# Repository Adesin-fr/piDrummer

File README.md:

# piDrummer

piDrummer is a DIY drum trigger device. it uses an Arduino and some basic components to get the signal from your pads (AKA triggers) and send them to a Raspberry Pi 3.

A Raspberry Pi 3 is used to play sounds according to the triggers you hit. 

Thanks to CPU power of a such board computer (4x1.2 Ghz), it is possible to play the best sound quality !

The rPi is also driving an ILI9341 TFT screen (320x240 pixels, can be found as cheap as 5$ on ebay ) and displays an interface that allows you to set up your different drum kits, the volume, sound effects (reverb, equalizer, etc...), and map each trigger to an instrument.

The goal is also to build an embedded linux, with the smallest possible kernel, allowing for very small boot time !

# piDrummer (Version Française)

piDrummer est un module de batterie électronique à fabriquer soi-même.

Il utilise un module Arduino et quelques composants pour récupérer le signal depuis les PADS (aussi appelés Triggers), et envoie ces informations à une carte Raspberry Pi 3.

La carte est alors utilisée pour jouer les sons en fonction des coups donnés.

Grâce à la puissance de calcul disponible sur la carte (4x1.2 Ghz), un rendu sonore de haute qualité est possible !

La carte rPi est aussi utilisée pour piloter un afficheur TFT (320x240 à base de puce ILI9341, qu'on peut acheter sur Ebay pour moins de 5€) afin de régler et choisir vos différents kits, le volume, les effets sonores (reverb, équaliseur, etc...) et mapper chaque trigger à un instrument.

Le but du projet est aussi de monter un système linux embarqué (linux Embedded) avec un noyau le plus léger possible, et un temps de démarrage le plus faible possible !

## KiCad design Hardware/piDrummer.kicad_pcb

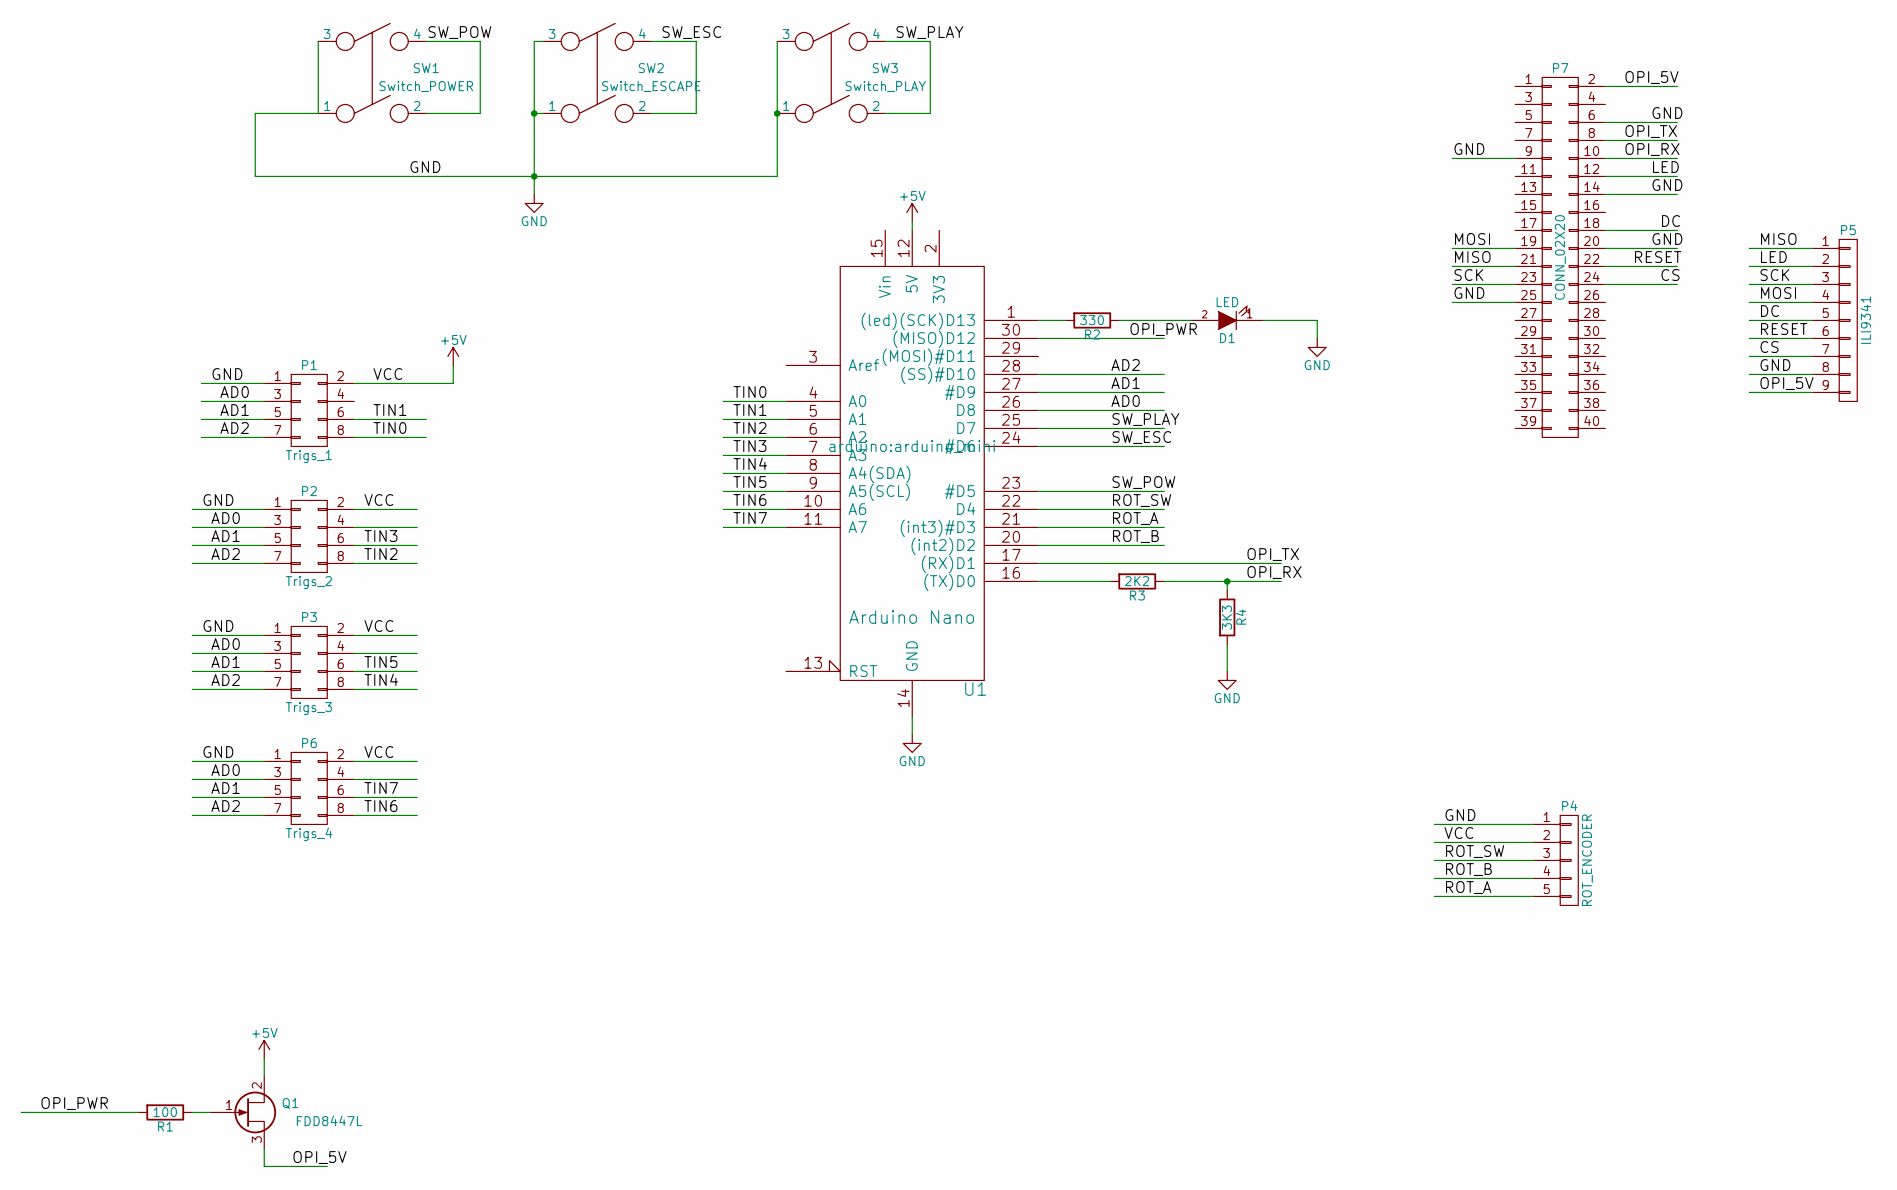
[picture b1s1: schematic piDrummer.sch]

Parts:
D1: LED; LED-3MM
P1: Trigs_1; Pin_Header_Straight_2x04
P2: Trigs_2; Pin_Header_Straight_2x04
P3: Trigs_3; Pin_Header_Straight_2x04
P4: ROT_ENCODER; Pin_Header_Straight_1x05
P5: ILI9341; Pin_Header_Straight_1x09
P6: Trigs_4; Pin_Header_Straight_2x04
P7: CONN_02X20; Pin_Header_Straight_2x20
Q1: FDD8447L; MOSFET_TO252
R1: 100; R4-LARGE_PADS
R2: 330; R4-LARGE_PADS
R3: 2K2; R4-LARGE_PADS
R4: 3K3; R4-LARGE_PADS
SW1: Switch_POWER; NetTie-III
SW2: Switch_ESCAPE; NetTie-III
SW3: Switch_PLAY; NetTie-III
U1: Arduino Nano; arduino_mini

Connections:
+5V: P1.2, P2.2, P3.2, P4.2, P6.2, Q1.2 (D), U1.12 (5V)
/AD0: P1.3, P2.3, P3.3, P6.3, U1.26 (D8)
/AD1: P1.5, P2.5, P3.5, P6.5, U1.27 (#D9)
/AD2: P1.7, P2.7, P3.7, P6.7, U1.28 ((SS)#D10)
/CS: P5.7, P7.24
/DC: P5.5, P7.18
/LED: P5.2, P7.12
/MISO: P5.1, P7.21
/MOSI: P5.4, P7.19
/OPI_5V: P5.9, P7.2, Q1.3 (S)
/OPI_PWR: R1.2, U1.30 ((MISO)D12)
/OPI_RX: P7.10, R3.1, R4.1
/OPI_TX: P7.8, U1.17 ((RX)D1)
/RESET: P5.6, P7.22
/ROT_A: P4.5, U1.21 ((int3)#D3)
/ROT_B: P4.4, U1.20 ((int2)D2)
/ROT_SW: P4.3, U1.22 (D4)
/SCK: P5.3, P7.23
/SW_ESC: SW2.2, SW2.4, U1.24 (#D6)
/SW_PLAY: SW3.2, SW3.4, U1.25 (D7)
/SW_POW: SW1.2, SW1.4, U1.23 (#D5)
/TIN0: P1.8, U1.4 (A0)
/TIN1: P1.6, U1.5 (A1)
/TIN2: P2.8, U1.6 (A2)
/TIN3: P2.6, U1.7 (A3)
/TIN4: P3.8, U1.8 (A4(SDA))
/TIN5: P3.6, U1.9 (A5(SCL))
/TIN6: P6.8, U1.10 (A6)
/TIN7: P6.6, U1.11 (A7)
GND: D1.1 (K), P1.1, P2.1, P3.1, P4.1, P5.8, P6.1, P7.6, P7.9, P7.14, P7.20, P7.25, R4.2, SW1.1, SW1.3, SW2.1, SW2.3, SW3.1, SW3.3, U1.14 (GND), U1.19 (GND)
unnamed: D1.2 (A), R2.1
unnamed: Q1.1 (G), R1.1
unnamed: R2.2, U1.1 ((led)(SCK)D13)
unnamed: R3.2, U1.16 ((TX)D0)

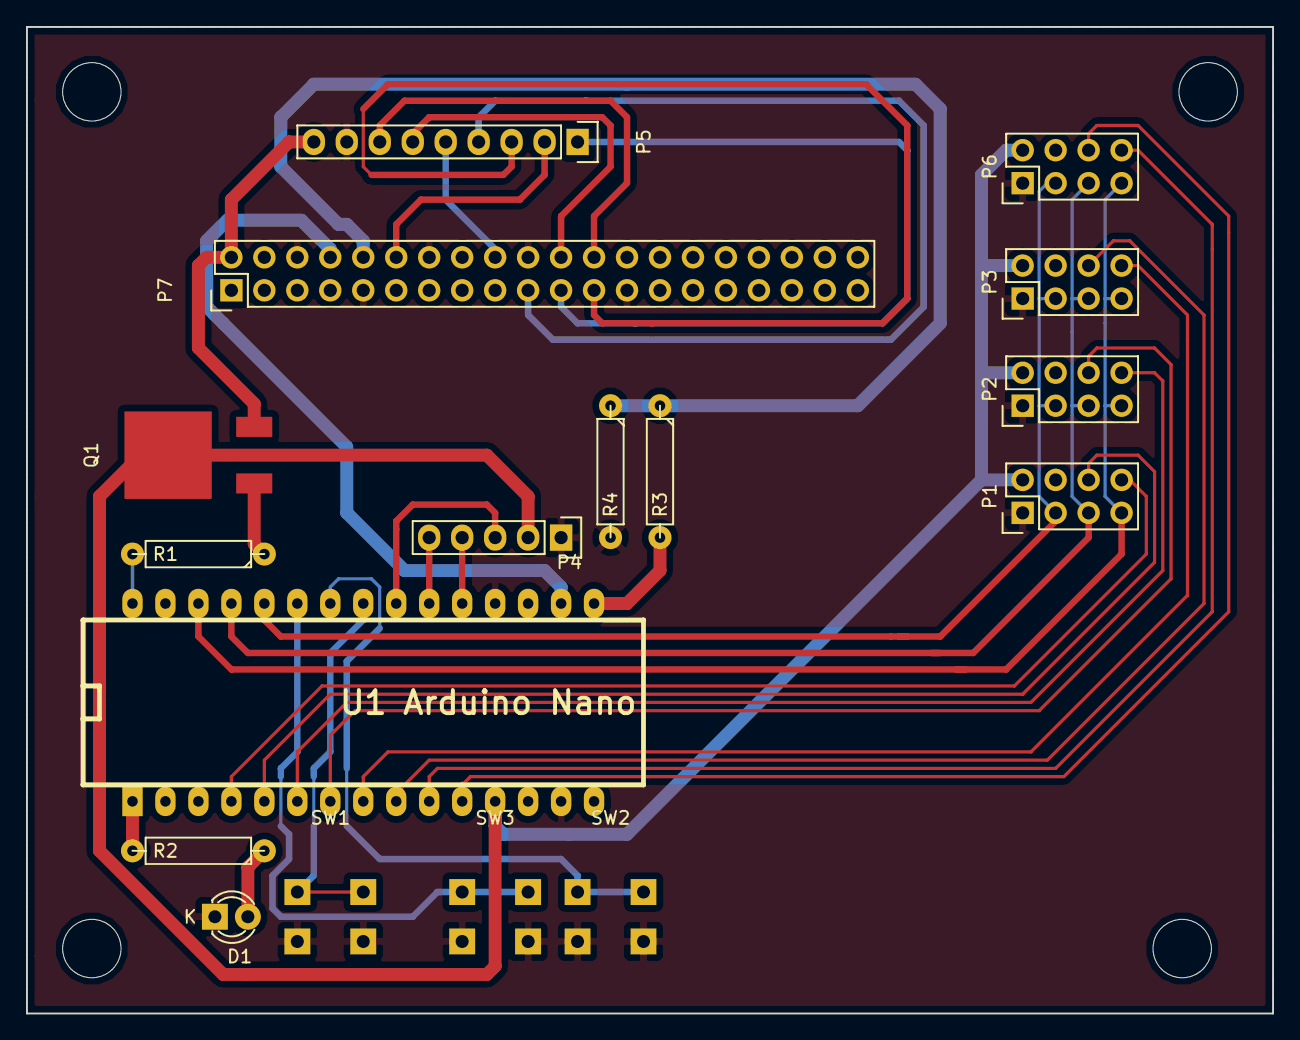
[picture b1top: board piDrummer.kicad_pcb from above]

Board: 2 copper layers, 96.0 x 76.0 mm, 17 parts (0 on the bottom side), 34 nets.

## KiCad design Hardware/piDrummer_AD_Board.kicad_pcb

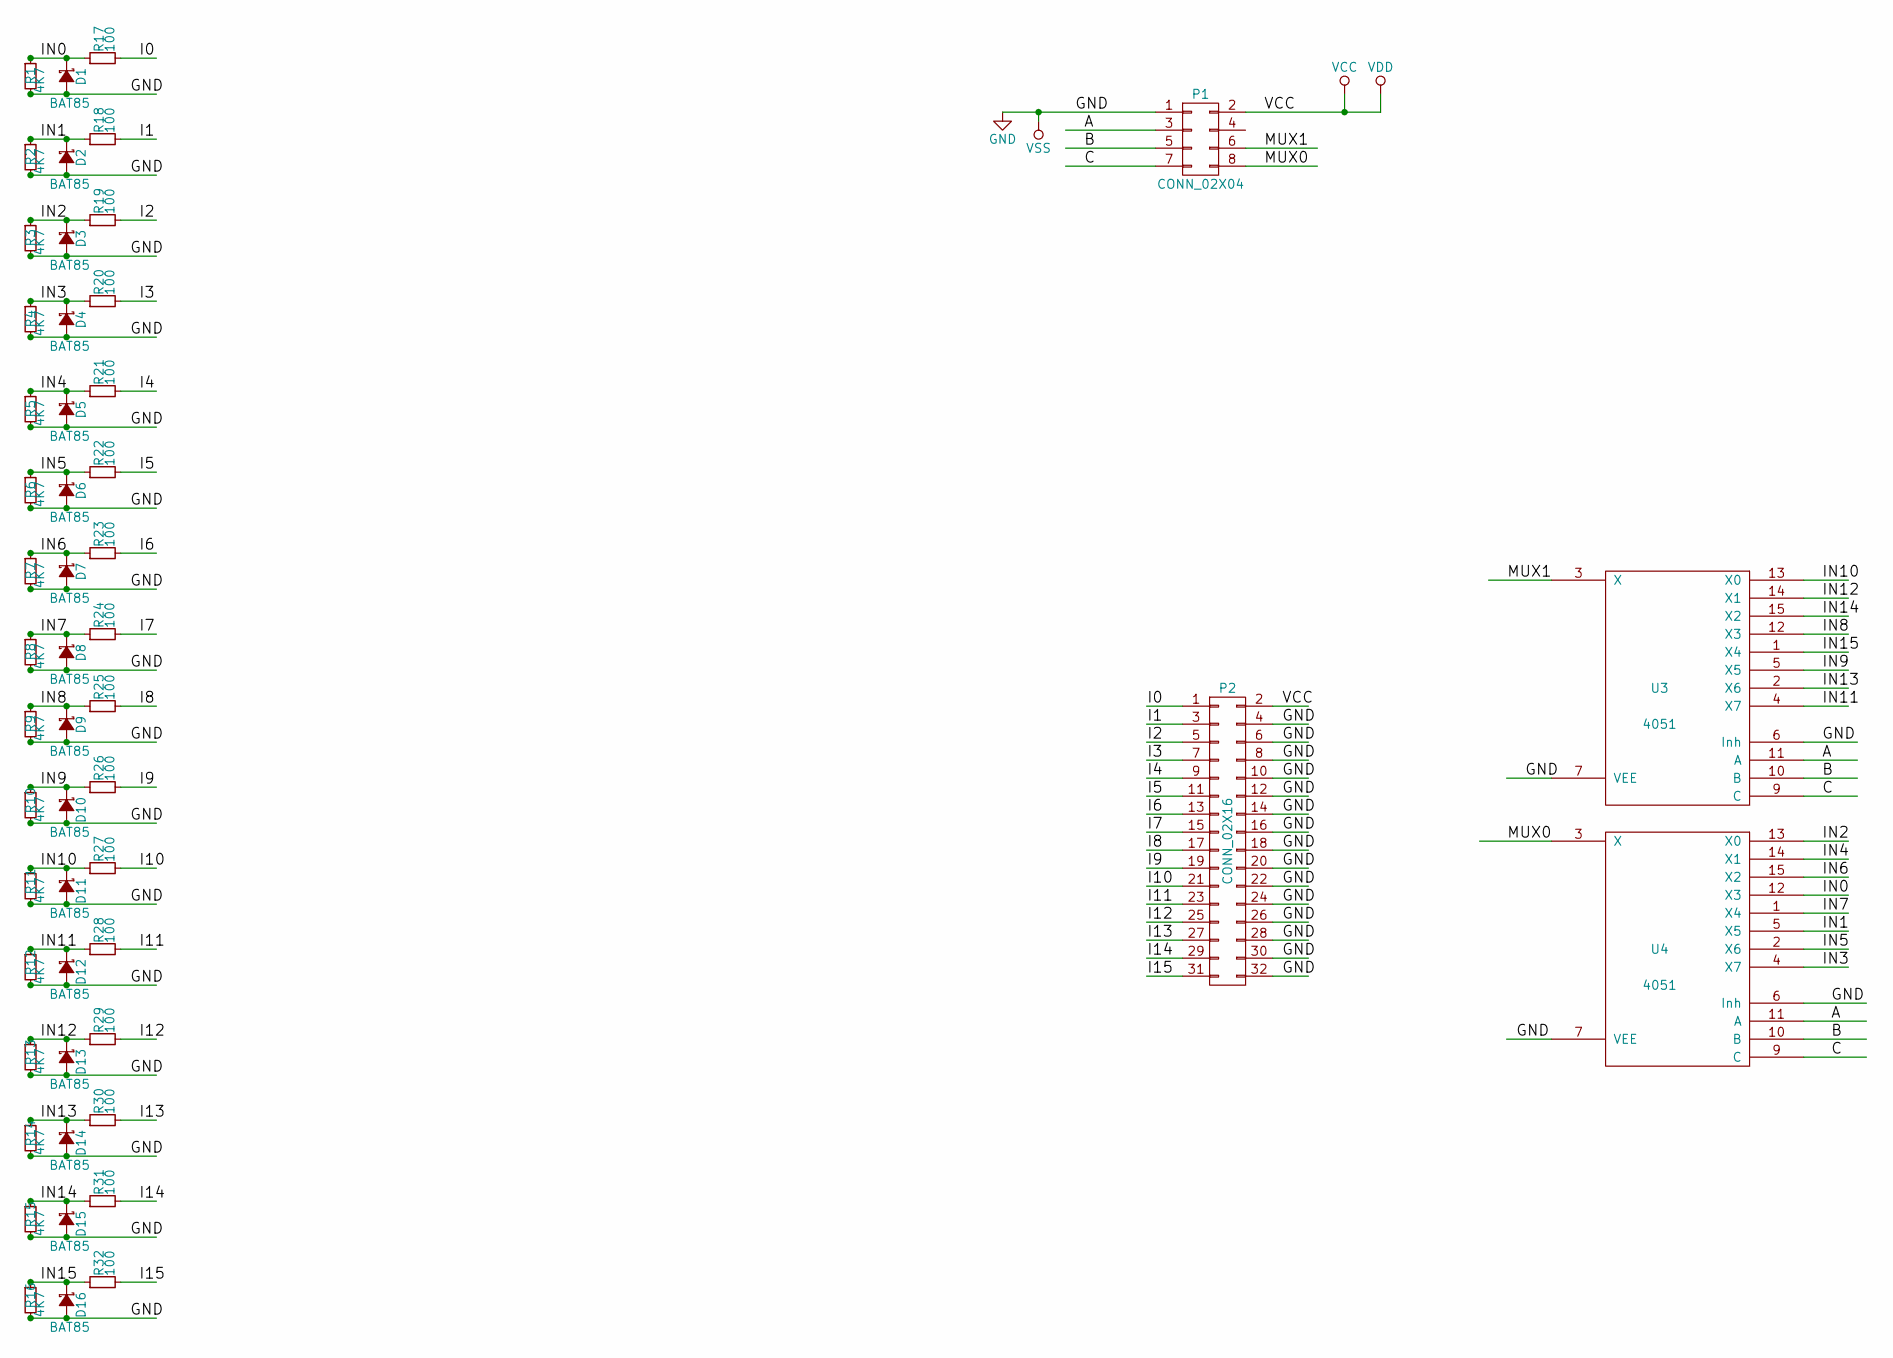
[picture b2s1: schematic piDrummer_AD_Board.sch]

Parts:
D1, D2, D3, D4, D5, D6, D7, D8, D9, D10, D11, D12, D13, D14, D15, D16: BAT85; Diode_DO-35_SOD27_Horizontal_RM10
P1: CONN_02X04; Header_Straight_8pins
P2: CONN_02X16; Header_Straight_32pins
R1, R2, R3, R4, R5, R6, R7, R8, R9, R10, R11, R12, R13, R14, R15, R16: 4K7; RES35
R17, R18, R19, R20, R21, R22, R23, R24, R25, R26, R27, R28, R29, R30, R31, R32: 100; RES35
U3, U4: 4051; DIP-16_W7.62mm_LongPads

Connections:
/A: P1.3, U3.11 (A), U4.11 (A)
/B: P1.5, U3.10 (B), U4.10 (B)
/C: P1.7, U3.9 (C), U4.9 (C)
/I0: P2.1, R17.2
/I1: P2.3, R18.2
/I2: P2.5, R19.2
/I3: P2.7, R20.2
/I4: P2.9, R21.2
/I5: P2.11, R22.2
/I6: P2.13, R23.2
/I7: P2.15, R24.2
/I8: P2.17, R25.2
/I9: P2.19, R26.2
/I10: P2.21, R27.2
/I11: P2.23, R28.2
/I12: P2.25, R29.2
/I13: P2.27, R30.2
/I14: P2.29, R31.2
/I15: P2.31, R32.2
/IN0: D1.1 (K), R1.1, R17.1, U4.12 (X3)
/IN1: D2.1 (K), R2.1, R18.1, U4.5 (X5)
/IN2: D3.1 (K), R3.1, R19.1, U4.13 (X0)
/IN3: D4.1 (K), R4.1, R20.1, U4.4 (X7)
/IN4: D5.1 (K), R5.1, R21.1, U4.14 (X1)
/IN5: D6.1 (K), R6.1, R22.1, U4.2 (X6)
/IN6: D7.1 (K), R7.1, R23.1, U4.15 (X2)
/IN7: D8.1 (K), R8.1, R24.1, U4.1 (X4)
/IN8: D9.1 (K), R9.1, R25.1, U3.12 (X3)
/IN9: D10.1 (K), R10.1, R26.1, U3.5 (X5)
/IN10: D11.1 (K), R11.1, R27.1, U3.13 (X0)
/IN11: D12.1 (K), R12.1, R28.1, U3.4 (X7)
/IN12: D13.1 (K), R13.1, R29.1, U3.14 (X1)
/IN13: D14.1 (K), R14.1, R30.1, U3.2 (X6)
/IN14: D15.1 (K), R15.1, R31.1, U3.15 (X2)
/IN15: D16.1 (K), R16.1, R32.1, U3.1 (X4)
/MUX0: P1.8, U4.3 (X)
/MUX1: P1.6, U3.3 (X)
GND: D1.2 (A), D2.2 (A), D3.2 (A), D4.2 (A), D5.2 (A), D6.2 (A), D7.2 (A), D8.2 (A), D9.2 (A), D10.2 (A), D11.2 (A), D12.2 (A), D13.2 (A), D14.2 (A), D15.2 (A), D16.2 (A), P1.1, P2.4, P2.6, P2.8, P2.10, P2.12, P2.14, P2.16, P2.18, P2.20, P2.22, P2.24, P2.26, P2.28, P2.30, P2.32, R1.2, R2.2, R3.2, R4.2, R5.2, R6.2, R7.2, R8.2, R9.2, R10.2, R11.2, R12.2, R13.2, R14.2, R15.2, R16.2, U3.6 (Inh), U3.7 (VEE), U3.8 (VSS), U4.6 (Inh), U4.7 (VEE), U4.8 (VSS)
VCC: P1.2, P2.2, U3.16 (VDD), U4.16 (VDD)

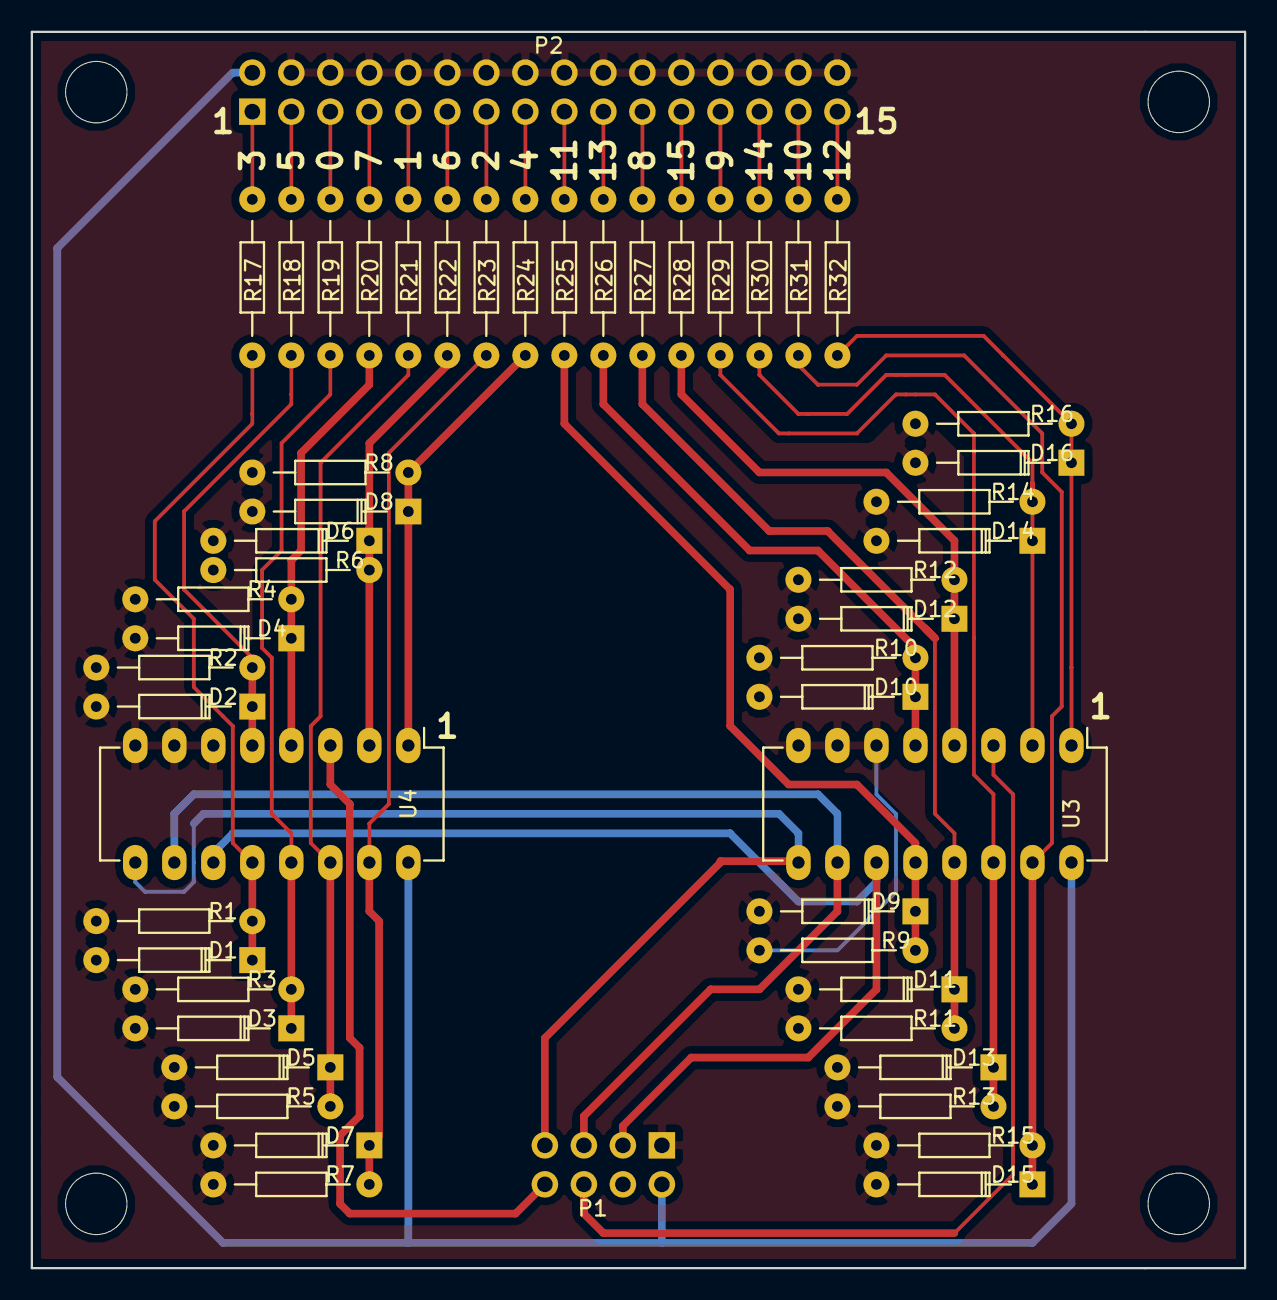
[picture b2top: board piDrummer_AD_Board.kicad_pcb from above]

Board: 2 copper layers, 79.0 x 80.5 mm, 52 parts (0 on the bottom side), 39 nets.

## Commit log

2016-07-20 Added current UI work
2016-07-21 Minor changes
2016-07-24 minor changes instrument loading
2016-07-25 * Cleaned destructors * Check if image exist before loading it * Check if font exist, exit if missing.
2016-07-25 Added missing files ?
2016-07-25 Many small changes
2016-07-26 Ajout fichier .cproject
2016-07-26 added file .project
2016-07-26 Added .gitignore file
2016-07-27 Added a bunch of little things
2016-07-27 Deleted debug objects
2016-07-27 Added begin of kit setup screen added .cproject file that was deleted
2016-07-28 Added TextLabel Class Redesigned serial port handling to set blocking event of 10ms in each loop. The blocking event exits if data is not available, or if data is there ! This drastically lower CPU u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
2016-07-29 Many small changes Using libsndfile to load samples. This allow us to load many more file formats (eg flac; etc...) BEWARE that using anything else than uncompressed file format will make loading slo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
2016-07-29 changed compilation options
2016-08-04 MANY changes ! * Optimized some functions which were returning copy of vectors instead of pointer to vector * Added histogram to main screen
2016-08-04 Changed histogram height
2016-08-04 Moved screen drawing function to a different thread. Since this function was eating about 5-6ms, this should lower the latency.
2016-08-05 Changed the multithreading gear : SDL doesn't like to be in a separate thread, so the "serial handling" stuff is now runned in a different thread. Running with an Alsa buffer size of 512 works great 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
2016-08-05 Added a "Font Store" to keep fonts loaded between each call Fixed samples loading with libsndfile
2016-08-05 Minor changes. Use of scrolling labels in lists
2016-08-10 Added Metronome class Added support for round robin samples !
2016-08-18 Added global settings menu.
2016-08-19 Added Signal Curve settings (show curve, change, edit points ! ) Added trigger settings to config file
2016-08-19 removed unused classe AudioEngine
2016-08-19 Added different actions for rotary knob on Main Screen
2016-09-12 Modified serial port settings
2016-09-12 Managed to get soloud library used without including the source :)
2016-09-12 Added makefile :)
2016-09-12 Fixed a NULL POINTER
2016-09-14 Added splash screen file Changed handling on CTRL-C which did not quitted SDL correctly.
2016-09-15 Renamed project! Goodbye urDrummer, say Hello to piDrummer !
2016-09-15 Cleaned some functions so the compiler won't complain about unused variables.
2016-09-15 Moved software in subfolder... Added hardware schematics !
2016-09-15 Added .cprojet and .project file
2016-09-15 Modified splash screen
2016-09-20 Added gerber output for hardware
2017-12-15 Added splash files and conversion tool.
2017-12-17 Added Arduino Firmware
2017-12-19 Added solound library inside project. Makes way more easy to compile !
2017-12-19 Added some code protection on ScreenDrawing when settings are empty.
2017-12-19 Added mention to used libraries
2017-12-19 Minor changes to main function
2017-12-19 Changed dependencies
2017-12-19 Changed arduino firmware to be compiled with Atom.io and platform.io
2017-12-20 Added Home folder (~/.piDrummer) and resource contents.
